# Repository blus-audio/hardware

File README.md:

# Blus hardware

This repository contains hardware designs for the blus series of audio equipment.

- The [blus mini](./blus-mini) - a small 4x25 W digital amplifier with DSP and various digital inputs.

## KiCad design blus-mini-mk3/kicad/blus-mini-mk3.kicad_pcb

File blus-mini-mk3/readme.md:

# Blus mini mk2

This small amplifier is ideally suited for stereo pairs of two-way speakers.

Find the [hardware design files](./kicad/) for reference.
It is required to flash the corresponding [firmware](https://github.com/blus-audio/firmware-rs).

## Features

- Source switching, digital signal processing, and more on a powerful STM32H723
- 4x25 W Class-D amplifiers - the [TI TAS2780](https://www.ti.com/product/TAS2780)
- USB Audio interface (UAC 1.0) with up to 48 kHz/32 bit audio
- Raspberry Pi header for direct I2S audio streaming
- S/PDIF input and output
- Auxiliary I2S input or output
- Full 32 bit digital audio chain with analog conversion only in the amplifiers

## State of development

The amplifier has been fully tested for an extended period of time.

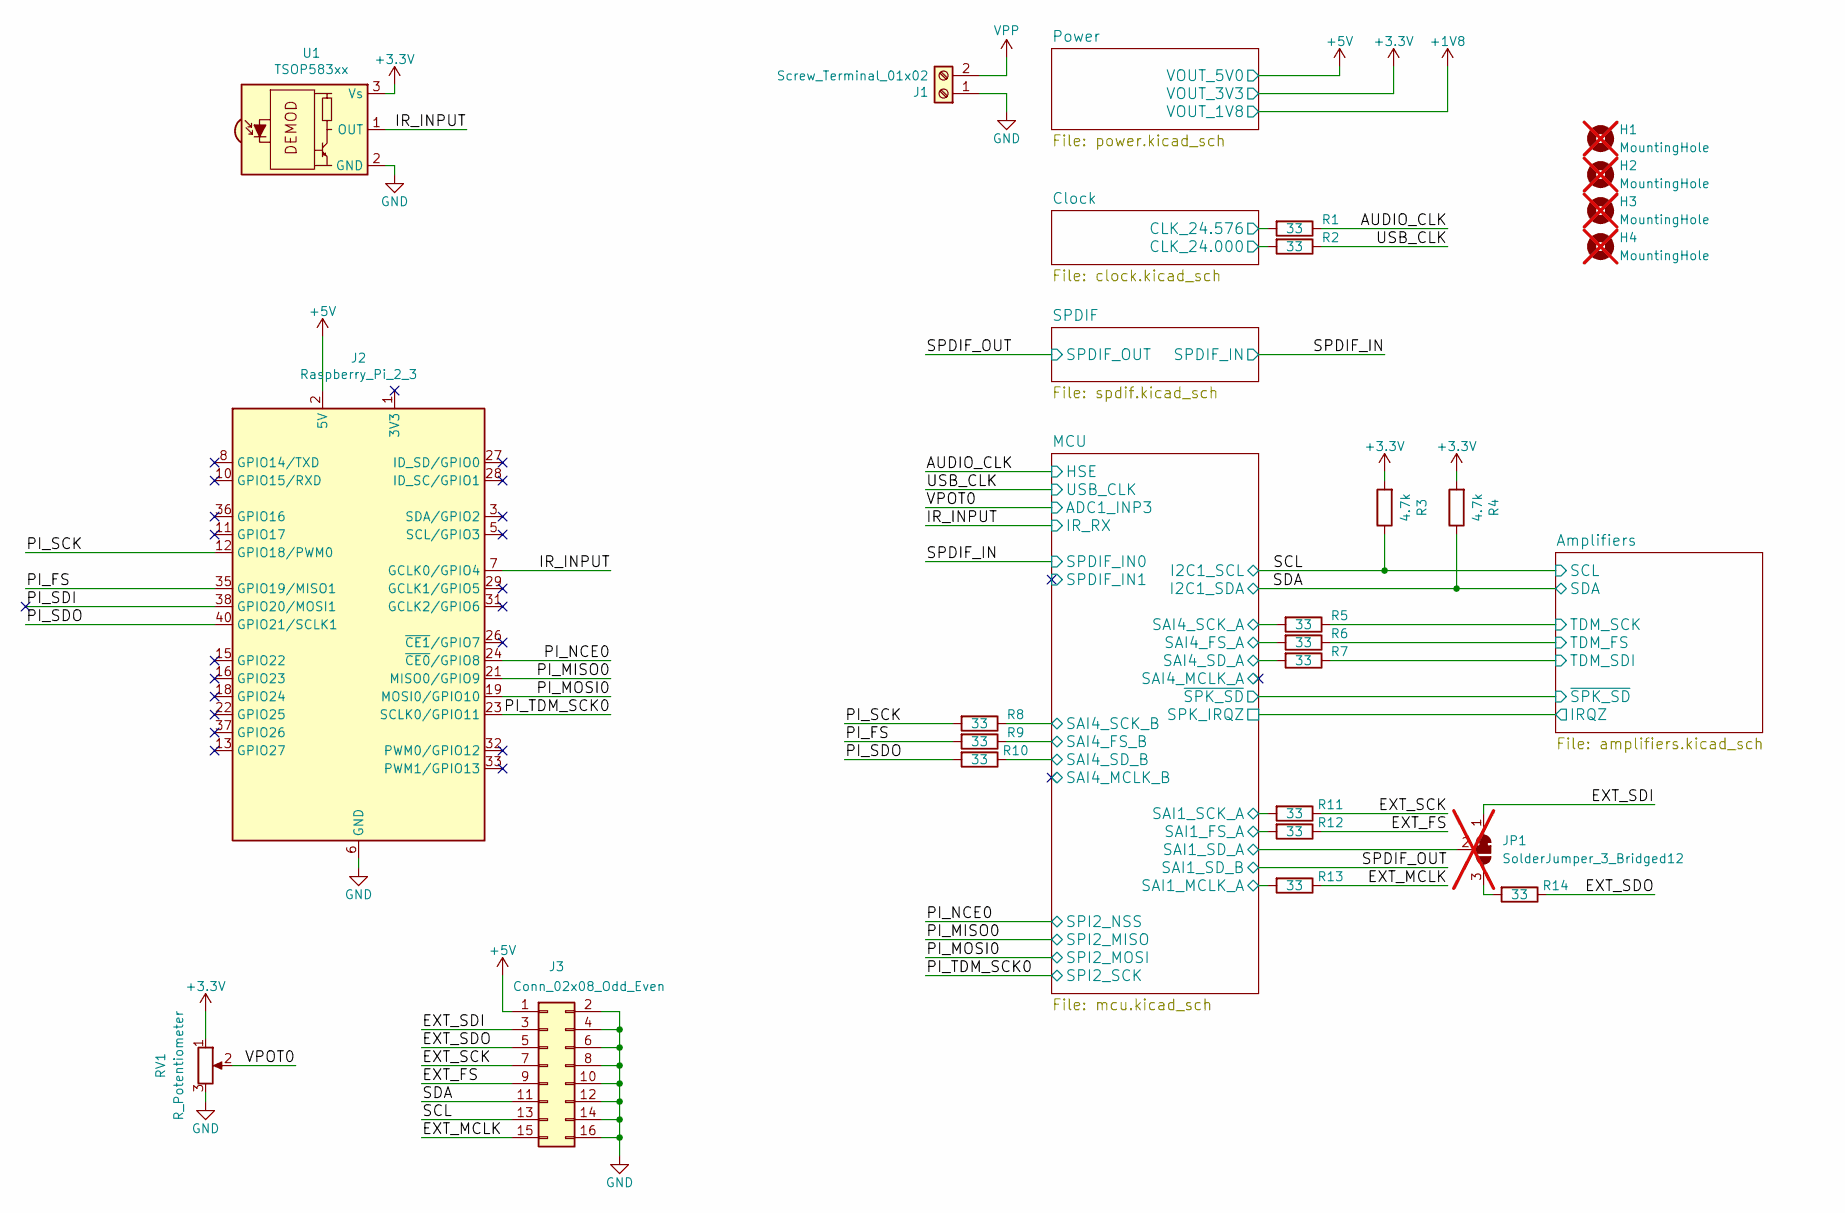
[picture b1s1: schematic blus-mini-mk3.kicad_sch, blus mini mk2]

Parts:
H1, H2, H3, H4: MountingHole; MountingHole_3.2mm_M3_ISO7380_Pad; not fitted
J1: Screw_Terminal_01x02; wuerth_691216410002
J2: Raspberry_Pi_2_3; PinSocket_2x20_P2.54mm_Vertical
J3: Conn_02x08_Odd_Even; IDC-Header_2x08_P2.54mm_Horizontal
JP1: SolderJumper_3_Bridged12; SolderJumper-3_P1.3mm_Bridged12_RoundedPad1.0x1.5mm; not fitted
R1, R2, R5, R6, R7, R8, R9, R10, R11, R12, R13, R14: 33; R_0402_1005Metric; MPN C25105
R3, R4: 4.7k; R_0402_1005Metric; MPN C25900
RV1: R_Potentiometer; Potentiometer_Bourns_PTV09A-1_Single_Vertical
U1: TSOP583xx; Vishay_MINICAST-3Pin

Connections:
+3.3V: R3.2, R4.2, RV1.1, U1.3 (Vs); also elsewhere on the board
+5V: J2.2 (5V), J2.4 (5V), J3.1; also elsewhere on the board
/AUDIO_CLK: R1.1; also elsewhere on the board
/Amplifiers/TDM_FS: R6.1; also elsewhere on the board
/Amplifiers/TDM_SCK: R5.1; also elsewhere on the board
/Amplifiers/TDM_SDI: R7.1; also elsewhere on the board
/Clock/CLK_24.000: R2.2; also elsewhere on the board
/Clock/CLK_24.576: R1.2; also elsewhere on the board
/EXT_FS: J3.9, R12.1
/EXT_MCLK: J3.15, R13.1
/EXT_SCK: J3.7, R11.1
/EXT_SDI: J3.3, JP1.1 (A)
/EXT_SDO: J3.5, R14.1
/IR_INPUT: J2.7 (GCLK0/GPIO4), U1.1 (OUT); also elsewhere on the board
/MCU/SAI1_FS_A: R12.2; also elsewhere on the board
/MCU/SAI1_MCLK_A: R13.2; also elsewhere on the board
/MCU/SAI1_SCK_A: R11.2; also elsewhere on the board
/MCU/SAI1_SD_A: JP1.2 (C); also elsewhere on the board
/MCU/SAI4_FS_A: R6.2; also elsewhere on the board
/MCU/SAI4_FS_B: R9.1; also elsewhere on the board
/MCU/SAI4_SCK_A: R5.2; also elsewhere on the board
/MCU/SAI4_SCK_B: R8.1; also elsewhere on the board
/MCU/SAI4_SD_A: R7.2; also elsewhere on the board
/MCU/SAI4_SD_B: R10.1; also elsewhere on the board
/PI_FS: J2.35 (GPIO19/MISO1), R9.2
/PI_MISO0: J2.21 (MISO0/GPIO9); also elsewhere on the board
/PI_MOSI0: J2.19 (MOSI0/GPIO10); also elsewhere on the board
/PI_NCE0: J2.24 (~CE0/GPIO8); also elsewhere on the board
/PI_SCK: J2.12 (GPIO18/PWM0), R8.2
/PI_SDI: J2.38 (GPIO20/MOSI1)
/PI_SDO: J2.40 (GPIO21/SCLK1), R10.2
/PI_TDM_SCK0: J2.23 (SCLK0/GPIO11); also elsewhere on the board
/SCL: J3.13, R3.1; also elsewhere on the board
/SDA: J3.11, R4.1; also elsewhere on the board
/USB_CLK: R2.1; also elsewhere on the board
/VPOT0: RV1.2; also elsewhere on the board
GND: J1.1, J2.6 (GND), J2.9 (GND), J2.14 (GND), J2.20 (GND), J2.25 (GND), J2.30 (GND), J2.34 (GND), J2.39 (GND), J3.2, J3.4, J3.6, J3.8, J3.10, J3.12, J3.14, J3.16, RV1.3, U1.2 (GND); also elsewhere on the board
unnamed: JP1.3 (B), R14.2
VPP: J1.2; also elsewhere on the board

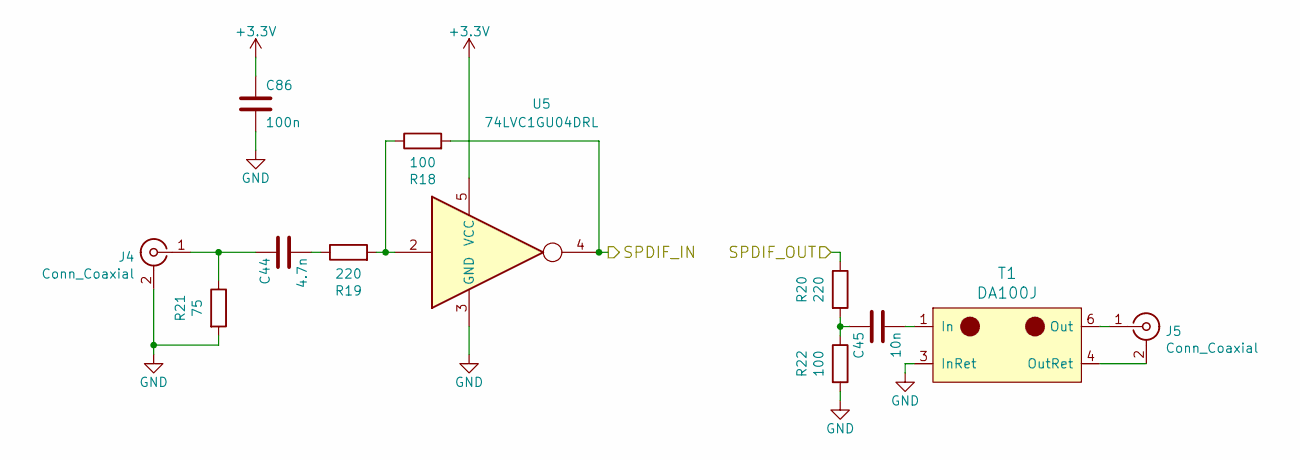
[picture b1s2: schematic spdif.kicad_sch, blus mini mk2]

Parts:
C44: 4.7n; C_0402_1005Metric
C45: 10n; C_0402_1005Metric; MPN C15195
C86: 100n; C_0402_1005Metric; MPN C307331
J4, J5: Conn_Coaxial; cui_rcj_02x
R18, R22: 100; R_0402_1005Metric; MPN C25076
R19, R20: 220; R_0402_1005Metric; MPN C25091
R21: 75; R_0402_1005Metric; MPN C25133
T1: DA100J; SOIC-6
U5: 74LVC1GU04DRL; SOT-553; MPN C2877548

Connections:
+3.3V: C86.1, U5.5 (VCC); also elsewhere on the board
/SPDIF_IN: R18.2, U5.4; also elsewhere on the board
/SPDIF_OUT: R20.1; also elsewhere on the board
GND: C86.2, J4.2 (Ext), R21.2, R22.2, T1.3 (InRet), U5.3 (GND); also elsewhere on the board
unnamed: C44.2, R19.1
unnamed: C45.1, R20.2, R22.1
unnamed: C44.1, J4.1 (In), R21.1
unnamed: J5.2 (Ext), T1.4 (OutRet)
unnamed: J5.1 (In), T1.6 (Out)
unnamed: R18.1, R19.2, U5.2
unnamed: C45.2, T1.1 (In)

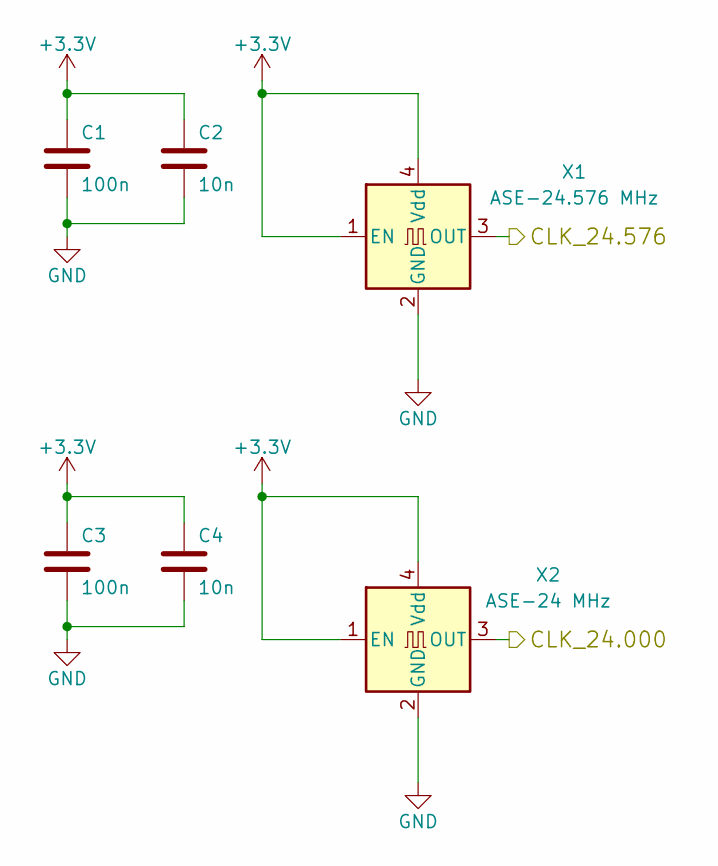
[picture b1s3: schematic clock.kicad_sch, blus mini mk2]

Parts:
C1, C3: 100n; C_0402_1005Metric; MPN C307331
C2, C4: 10n; C_0402_1005Metric; MPN C15195
X1: ASE-24.576 MHz; Oscillator_SMD_Abracon_ASE-4Pin_3.2x2.5mm
X2: ASE-24 MHz; Oscillator_SMD_Abracon_ASE-4Pin_3.2x2.5mm; MPN C507379

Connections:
+3.3V: C1.1, C2.1, C3.1, C4.1, X1.1 (EN), X1.4 (Vdd), X2.1 (EN), X2.4 (Vdd); also elsewhere on the board
/Clock/CLK_24.000: X2.3 (OUT); also elsewhere on the board
/Clock/CLK_24.576: X1.3 (OUT); also elsewhere on the board
GND: C1.2, C2.2, C3.2, C4.2, X1.2 (GND), X2.2 (GND); also elsewhere on the board

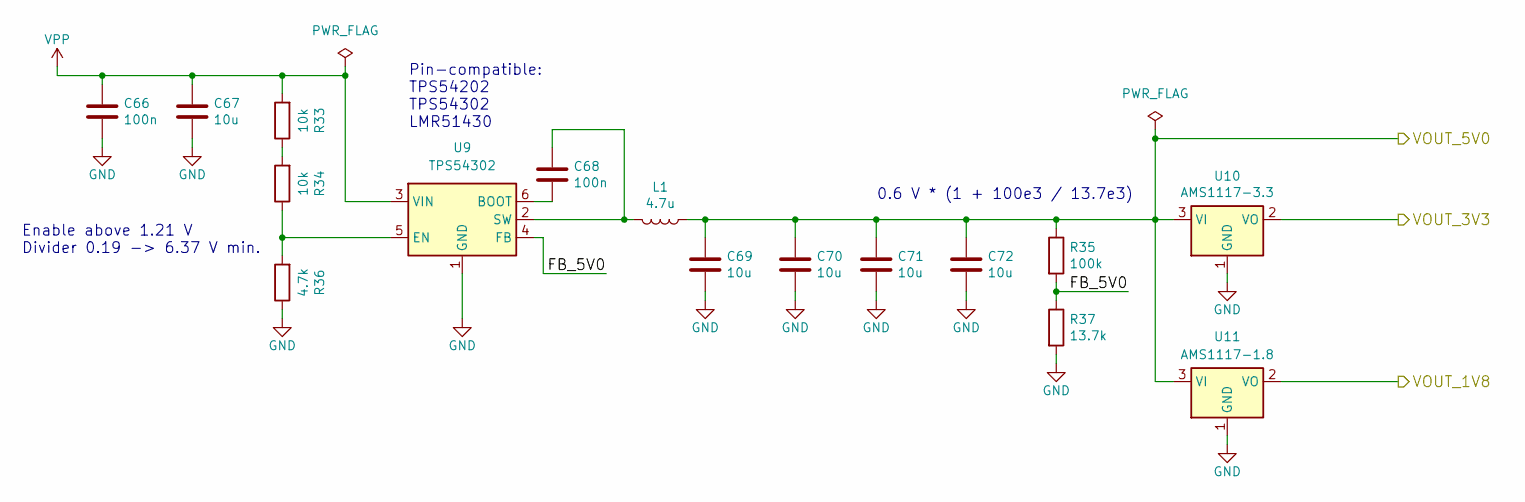
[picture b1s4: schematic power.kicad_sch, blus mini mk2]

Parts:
C66, C68: 100n; C_0402_1005Metric; MPN C307331
C67, C69, C70, C71, C72: 10u; C_1206_3216Metric; MPN C13585
L1: 4.7u; L_Abracon_ASPI-0630LR; MPN C167220
R33, R34: 10k; R_0402_1005Metric; MPN C25744
R35: 100k; R_0402_1005Metric; MPN C25741
R36: 4.7k; R_0402_1005Metric; MPN C25900
R37: 13.7k; R_0402_1005Metric
U9: TPS54302; SOT-23-6; MPN C311983; JLCPCB Rotation Offset -90
U10: AMS1117-3.3; SOT-223-3_TabPin2; MPN C6186
U11: AMS1117-1.8; SOT-223-3_TabPin2; MPN C6185

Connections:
+1V8: U11.2 (VO); also elsewhere on the board
+3.3V: U10.2 (VO); also elsewhere on the board
+5V: C69.1, C70.1, C71.1, C72.1, L1.1, R35.1, U10.3 (VI), U11.3 (VI); also elsewhere on the board
/Power/FB_5V0: R35.2, R37.1, U9.4 (FB)
GND: C66.2, C67.2, C69.2, C70.2, C71.2, C72.2, R36.1, R37.2, U9.1 (GND), U10.1 (GND), U11.1 (GND); also elsewhere on the board
unnamed: R33.1, R34.2
unnamed: C68.2, U9.6 (BOOT)
unnamed: R34.1, R36.2, U9.5 (EN)
unnamed: C68.1, L1.2, U9.2 (SW)
VPP: C66.1, C67.1, R33.2, U9.3 (VIN); also elsewhere on the board

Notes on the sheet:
0.6 V * (1 + 100e3 / 13.7e3)
Pin-compatible: TPS54202 TPS54302 LMR51430
Enable above 1.21 V Divider 0.19 -> 6.37 V min.

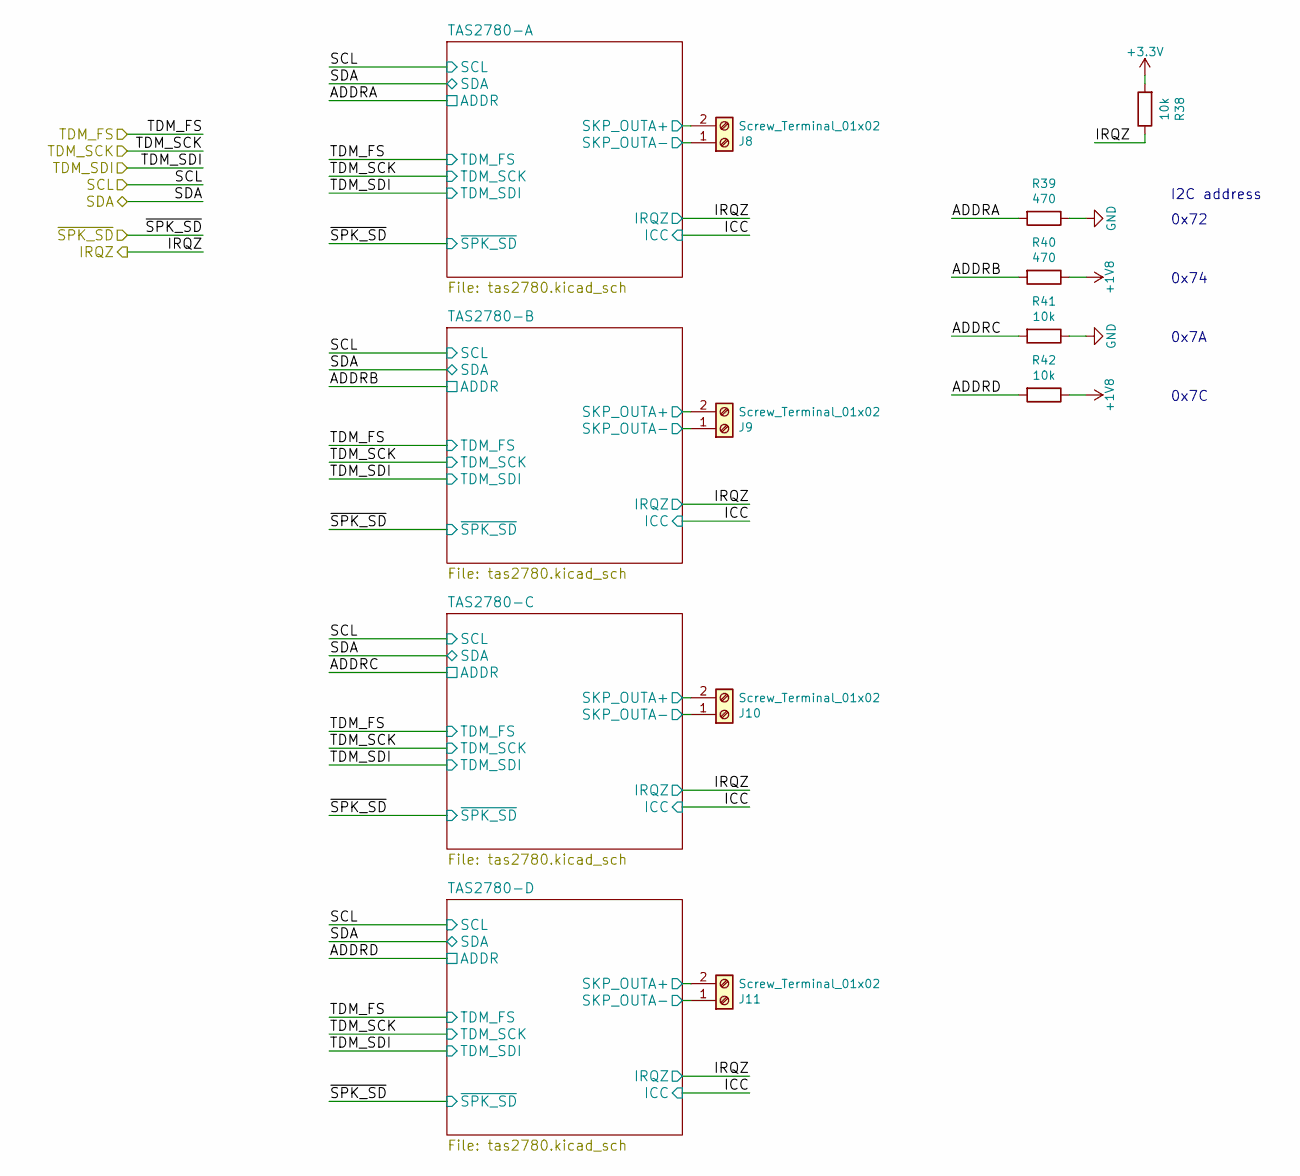
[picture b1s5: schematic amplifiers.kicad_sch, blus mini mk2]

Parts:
J8, J9, J10, J11: Screw_Terminal_01x02; wuerth_691216410002
R38, R41, R42: 10k; R_0402_1005Metric; MPN C25744
R39, R40: 470; R_0402_1005Metric; MPN C25117

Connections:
+1V8: R40.1, R42.1; also elsewhere on the board
+3.3V: R38.2; also elsewhere on the board
/Amplifiers/ADDRA: R39.2; also elsewhere on the board
/Amplifiers/ADDRB: R40.2; also elsewhere on the board
/Amplifiers/ADDRC: R41.2; also elsewhere on the board
/Amplifiers/ADDRD: R42.2; also elsewhere on the board
/Amplifiers/IRQZ: R38.1; also elsewhere on the board
/Amplifiers/TAS2780-A/SKP_OUTA+: J8.2; also elsewhere on the board
/Amplifiers/TAS2780-A/SKP_OUTA-: J8.1; also elsewhere on the board
/Amplifiers/TAS2780-B/SKP_OUTA+: J9.2; also elsewhere on the board
/Amplifiers/TAS2780-B/SKP_OUTA-: J9.1; also elsewhere on the board
/Amplifiers/TAS2780-C/SKP_OUTA+: J10.2; also elsewhere on the board
/Amplifiers/TAS2780-C/SKP_OUTA-: J10.1; also elsewhere on the board
/Amplifiers/TAS2780-D/SKP_OUTA+: J11.2; also elsewhere on the board
/Amplifiers/TAS2780-D/SKP_OUTA-: J11.1; also elsewhere on the board
GND: R39.1, R41.1; also elsewhere on the board

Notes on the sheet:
0x7C
0x72
0x7A
I2C address
0x74

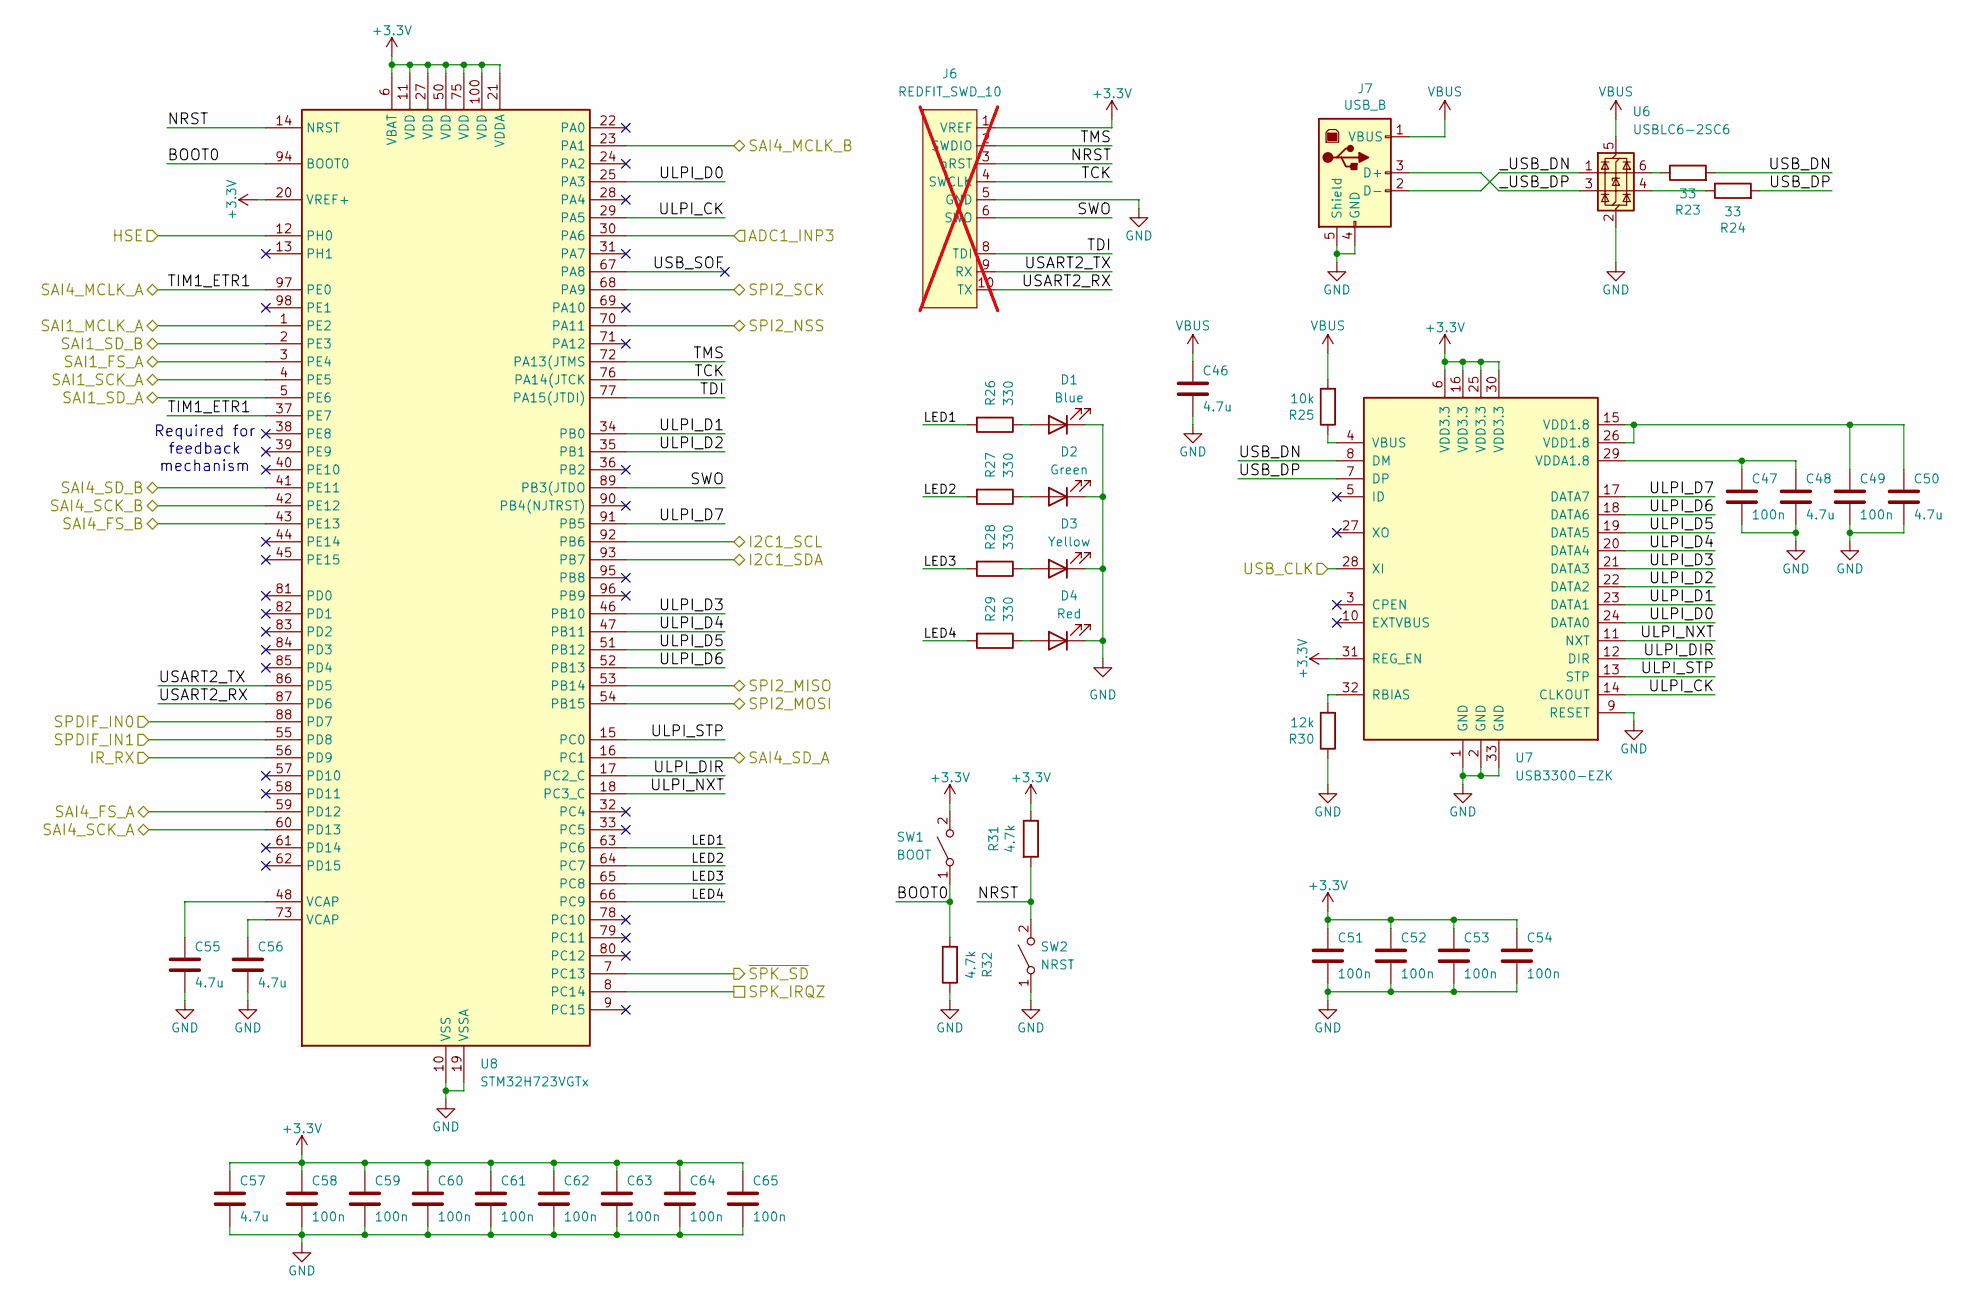
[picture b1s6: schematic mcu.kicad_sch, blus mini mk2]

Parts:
C46, C48, C50, C55, C56, C57: 4.7u; C_0805_2012Metric; MPN C1779
C47, C49, C51, C52, C53, C54, C58, C59, C60, C61, C62, C63, C64, C65: 100n; C_0402_1005Metric; MPN C307331
D1: Blue; LED_0603_1608Metric; MPN C72041
D2: Green; LED_0603_1608Metric; MPN C72043
D3: Yellow; LED_0603_1608Metric; MPN C72038
D4: Red; LED_0603_1608Metric; MPN C2286
J6: REDFIT_SWD_10; WR-WST REDFIT IDC 6 10 DBG; not fitted
J7: USB_B; USB_B_TE_5787834_Vertical; MPN C592900
R23, R24: 33; R_0402_1005Metric; MPN C25105
R25: 10k; R_0402_1005Metric; MPN C25744
R26, R27, R28, R29: 330; R_0402_1005Metric; MPN C25104
R30: 12k; R_0402_1005Metric; MPN C25752
R31, R32: 4.7k; R_0402_1005Metric; MPN C25900
SW1: BOOT; SW_SPST_TL3342; MPN C318884
SW2: NRST; SW_SPST_TL3342; MPN C318884
U6: USBLC6-2SC6; SOT-23-6; MPN C7519; JLCPCB Rotation Offset 90
U7: USB3300-EZK; QFN-32-1EP_5x5mm_P0.5mm_EP3.45x3.45mm; MPN C108383; JLCPCB Rotation Offset 180
U8: STM32H723VGTx; LQFP-100_14x14mm_P0.5mm; MPN C730142

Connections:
+3.3V: C51.1, C52.1, C53.1, C54.1, C57.1, C58.1, C59.1, C60.1, C61.1, C62.1, C63.1, C64.1, C65.1, J6.1 (VREF), R31.1, SW1.2 (B), U7.6 (VDD3.3), U7.16 (VDD3.3), U7.25 (VDD3.3), U7.30 (VDD3.3), U7.31 (REG_EN), U8.6 (VBAT), U8.11 (VDD), U8.20 (VREF+), U8.21 (VDDA), U8.27 (VDD), U8.50 (VDD), U8.75 (VDD), U8.100 (VDD); also elsewhere on the board
/AUDIO_CLK: U8.12 (PH0); also elsewhere on the board
/Amplifiers/IRQZ: U8.8 (PC14); also elsewhere on the board
/Amplifiers/~SPK_SD: U8.7 (PC13); also elsewhere on the board
/IR_INPUT: U8.56 (PD9); also elsewhere on the board
/MCU/BOOT0: R32.2, SW1.1 (A), U8.94 (BOOT0)
/MCU/LED1: R26.2, U8.63 (PC6)
/MCU/LED2: R27.2, U8.64 (PC7)
/MCU/LED3: R28.2, U8.65 (PC8)
/MCU/LED4: R29.2, U8.66 (PC9)
/MCU/NRST: J6.3 (nRST), R31.2, SW2.2 (B), U8.14 (NRST)
/MCU/SAI1_FS_A: U8.3 (PE4); also elsewhere on the board
/MCU/SAI1_MCLK_A: U8.1 (PE2); also elsewhere on the board
/MCU/SAI1_SCK_A: U8.4 (PE5); also elsewhere on the board
/MCU/SAI1_SD_A: U8.5 (PE6); also elsewhere on the board
/MCU/SAI4_FS_A: U8.59 (PD12); also elsewhere on the board
/MCU/SAI4_FS_B: U8.43 (PE13); also elsewhere on the board
/MCU/SAI4_MCLK_B: U8.23 (PA1)
/MCU/SAI4_SCK_A: U8.60 (PD13); also elsewhere on the board
/MCU/SAI4_SCK_B: U8.42 (PE12); also elsewhere on the board
/MCU/SAI4_SD_A: U8.16 (PC1); also elsewhere on the board
/MCU/SAI4_SD_B: U8.41 (PE11); also elsewhere on the board
/MCU/SPDIF_IN1: U8.55 (PD8)
/MCU/SWO: J6.6 (SWO), U8.89 (PB3(JTDO)
/MCU/TCK: J6.4 (SWCLK), U8.76 (PA14(JTCK)
/MCU/TDI: J6.8 (TDI), U8.77 (PA15(JTDI))
/MCU/TIM1_ETR1: U8.37 (PE7), U8.97 (PE0)
/MCU/TMS: J6.2 (SWDIO), U8.72 (PA13(JTMS)
/MCU/ULPI_CK: U7.14 (CLKOUT), U8.29 (PA5)
/MCU/ULPI_D0: U7.24 (DATA0), U8.25 (PA3)
/MCU/ULPI_D1: U7.23 (DATA1), U8.34 (PB0)
/MCU/ULPI_D2: U7.22 (DATA2), U8.35 (PB1)
/MCU/ULPI_D3: U7.21 (DATA3), U8.46 (PB10)
/MCU/ULPI_D4: U7.20 (DATA4), U8.47 (PB11)
/MCU/ULPI_D5: U7.19 (DATA5), U8.51 (PB12)
/MCU/ULPI_D6: U7.18 (DATA6), U8.52 (PB13)
/MCU/ULPI_D7: U7.17 (DATA7), U8.91 (PB5)
/MCU/ULPI_DIR: U7.12 (DIR), U8.17 (PC2_C)
/MCU/ULPI_NXT: U7.11 (NXT), U8.18 (PC3_C)
/MCU/ULPI_STP: U7.13 (STP), U8.15 (PC0)
/MCU/USART2_RX: J6.10 (TX), U8.87 (PD6)
/MCU/USART2_TX: J6.9 (RX), U8.86 (PD5)
/MCU/USB_DN: R23.2, U7.8 (DM)
/MCU/USB_DP: R24.2, U7.7 (DP)
/MCU/USB_SOF: U8.67 (PA8)
/MCU/_USB_DN: J7.2 (D-), U6.1 (I/O1)
/MCU/_USB_DP: J7.3 (D+), U6.3 (I/O2)
/PI_MISO0: U8.53 (PB14); also elsewhere on the board
/PI_MOSI0: U8.54 (PB15); also elsewhere on the board
/PI_NCE0: U8.70 (PA11); also elsewhere on the board
/PI_TDM_SCK0: U8.68 (PA9); also elsewhere on the board
/SCL: U8.92 (PB6); also elsewhere on the board
/SDA: U8.93 (PB7); also elsewhere on the board
/SPDIF_IN: U8.88 (PD7); also elsewhere on the board
/SPDIF_OUT: U8.2 (PE3); also elsewhere on the board
/USB_CLK: U7.28 (XI); also elsewhere on the board
/VPOT0: U8.30 (PA6); also elsewhere on the board
GND: C46.2, C47.2, C48.2, C49.2, C50.2, C51.2, C52.2, C53.2, C54.2, C55.2, C56.2, C57.2, C58.2, C59.2, C60.2, C61.2, C62.2, C63.2, C64.2, C65.2, D1.1 (K), D2.1 (K), D3.1 (K), D4.1 (K), J6.5 (GND), J7.4 (GND), J7.5 (Shield), R30.1, R32.1, SW2.1 (A), U6.2 (GND), U7.1 (GND), U7.2 (GND), U7.9 (RESET), U7.33 (GND), U8.10 (VSS), U8.19 (VSSA), U8.26 (VSS), U8.49 (VSS), U8.74 (VSS), U8.99 (VSS); also elsewhere on the board
unnamed: C49.1, C50.1, U7.15 (VDD1.8), U7.26 (VDD1.8)
unnamed: C55.1, U8.48 (VCAP)
unnamed: C56.1, U8.73 (VCAP)
unnamed: D1.2 (A), R26.1
unnamed: D2.2 (A), R27.1
unnamed: D3.2 (A), R28.1
unnamed: D4.2 (A), R29.1
unnamed: R23.1, U6.6 (I/O1)
unnamed: R24.1, U6.4 (I/O2)
unnamed: R30.2, U7.32 (RBIAS)
unnamed: R25.1, U7.4 (VBUS)
unnamed: C47.1, C48.1, U7.29 (VDDA1.8)
VBUS: C46.1, J7.1 (VBUS), R25.2, U6.5 (VBUS)

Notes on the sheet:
Required for feedback mechanism

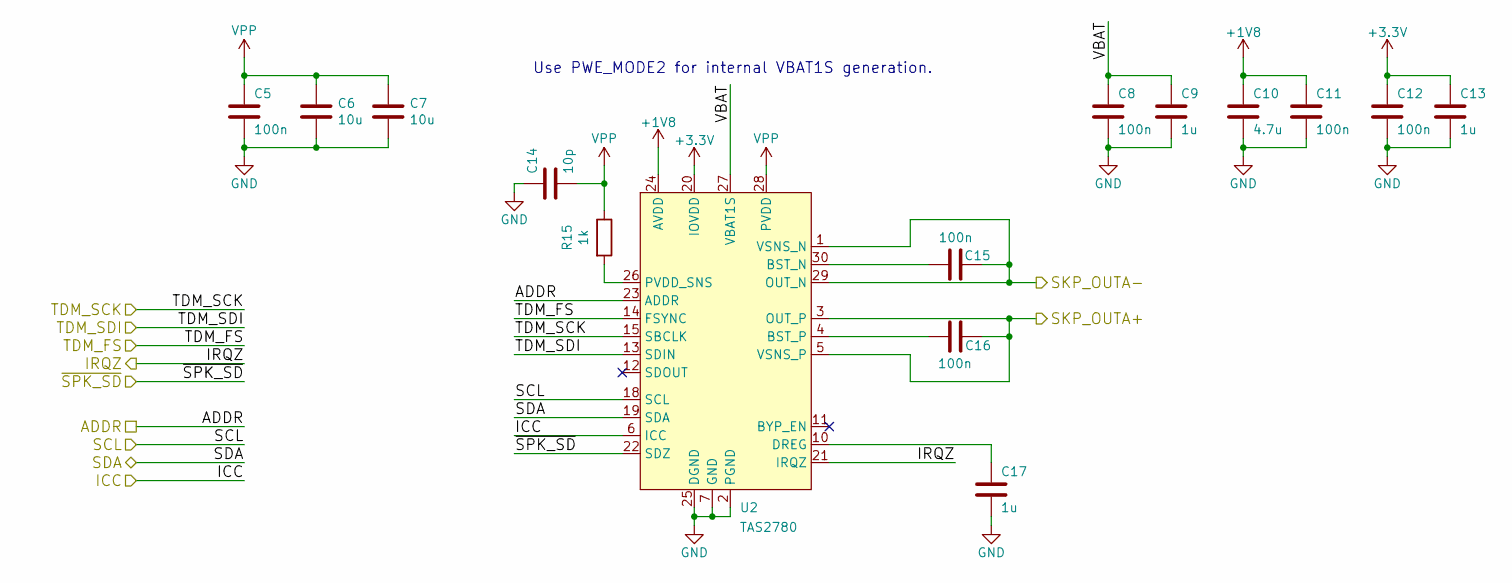
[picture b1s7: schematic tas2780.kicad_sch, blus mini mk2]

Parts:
C5, C8, C11, C12, C15, C16: 100n; C_0402_1005Metric; MPN C307331
C6, C7: 10u; C_1206_3216Metric; MPN C13585
C9, C13, C17: 1u; C_0603_1608Metric; MPN C15849
C10: 4.7u; C_0805_2012Metric; MPN C1779
C14: 10p; C_0402_1005Metric; MPN C32949
R15: 1k; R_0402_1005Metric; MPN C11702
U2: TAS2780; TI-30-Pin-HR-QFN; MPN C5214951

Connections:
+1V8: C10.1, C11.1, U2.24 (AVDD); also elsewhere on the board
+3.3V: C12.1, C13.1, U2.20 (IOVDD); also elsewhere on the board
/Amplifiers/ADDRA: U2.23 (ADDR); also elsewhere on the board
/Amplifiers/ICC: U2.6 (ICC); also elsewhere on the board
/Amplifiers/IRQZ: U2.21 (IRQZ); also elsewhere on the board
/Amplifiers/TAS2780-A/SKP_OUTA+: C16.1, U2.3 (OUT_P), U2.5 (VSNS_P); also elsewhere on the board
/Amplifiers/TAS2780-A/SKP_OUTA-: C15.2, U2.1 (VSNS_N), U2.29 (OUT_N); also elsewhere on the board
/Amplifiers/TAS2780-A/VBAT: C8.1, C9.1, U2.27 (VBAT1S)
/Amplifiers/TDM_FS: U2.14 (FSYNC); also elsewhere on the board
/Amplifiers/TDM_SCK: U2.15 (SBCLK); also elsewhere on the board
/Amplifiers/TDM_SDI: U2.13 (SDIN); also elsewhere on the board
/Amplifiers/~SPK_SD: U2.22 (SDZ); also elsewhere on the board
/SCL: U2.18 (SCL); also elsewhere on the board
/SDA: U2.19 (SDA); also elsewhere on the board
GND: C5.2, C6.2, C7.2, C8.2, C9.2, C10.2, C11.2, C12.2, C13.2, C14.1, C17.2, U2.2 (PGND), U2.7 (GND), U2.25 (DGND); also elsewhere on the board
unnamed: C15.1, U2.30 (BST_N)
unnamed: C16.2, U2.4 (BST_P)
unnamed: C17.1, U2.10 (DREG)
unnamed: R15.2, U2.26 (PVDD_SNS)
VPP: C5.1, C6.1, C7.1, C14.2, R15.1, U2.28 (PVDD); also elsewhere on the board

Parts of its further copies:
C18, C21, C24, C25, C28, C29, C31, C34, C37, C38, C41, C42, C73, C76, C79, C80, C83, C84: 100n; C_0402_1005Metric; MPN C307331
C19, C20, C32, C33, C74, C75: 10u; C_1206_3216Metric; MPN C13585
C22, C26, C30, C35, C39, C43, C77, C81, C85: 1u; C_0603_1608Metric; MPN C15849
C23, C36, C78: 4.7u; C_0805_2012Metric; MPN C1779
C27, C40, C82: 10p; C_0402_1005Metric; MPN C32949
R16, R17, R43: 1k; R_0402_1005Metric; MPN C11702
U3, U4, U12: TAS2780; TI-30-Pin-HR-QFN; MPN C5214951

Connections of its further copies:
+1V8: C23.1, C24.1, C36.1, C37.1, C78.1, C79.1, U3.24 (AVDD), U4.24 (AVDD), U12.24 (AVDD); also elsewhere on the board
+3.3V: C25.1, C26.1, C38.1, C39.1, C80.1, C81.1, U3.20 (IOVDD), U4.20 (IOVDD), U12.20 (IOVDD); also elsewhere on the board
/Amplifiers/ADDRB: U12.23 (ADDR); also elsewhere on the board
/Amplifiers/ADDRC: U3.23 (ADDR); also elsewhere on the board
/Amplifiers/ADDRD: U4.23 (ADDR); also elsewhere on the board
/Amplifiers/ICC: U3.6 (ICC), U4.6 (ICC), U12.6 (ICC); also elsewhere on the board
/Amplifiers/IRQZ: U3.21 (IRQZ), U4.21 (IRQZ), U12.21 (IRQZ); also elsewhere on the board
/Amplifiers/TAS2780-B/SKP_OUTA+: C84.1, U12.3 (OUT_P), U12.5 (VSNS_P); also elsewhere on the board
/Amplifiers/TAS2780-B/SKP_OUTA-: C83.2, U12.1 (VSNS_N), U12.29 (OUT_N); also elsewhere on the board
/Amplifiers/TAS2780-B/VBAT: C76.1, C77.1, U12.27 (VBAT1S)
/Amplifiers/TAS2780-C/SKP_OUTA+: C29.1, U3.3 (OUT_P), U3.5 (VSNS_P); also elsewhere on the board
/Amplifiers/TAS2780-C/SKP_OUTA-: C28.2, U3.1 (VSNS_N), U3.29 (OUT_N); also elsewhere on the board
/Amplifiers/TAS2780-C/VBAT: C21.1, C22.1, U3.27 (VBAT1S)
/Amplifiers/TAS2780-D/SKP_OUTA+: C42.1, U4.3 (OUT_P), U4.5 (VSNS_P); also elsewhere on the board
/Amplifiers/TAS2780-D/SKP_OUTA-: C41.2, U4.1 (VSNS_N), U4.29 (OUT_N); also elsewhere on the board
/Amplifiers/TAS2780-D/VBAT: C34.1, C35.1, U4.27 (VBAT1S)
/Amplifiers/TDM_FS: U3.14 (FSYNC), U4.14 (FSYNC), U12.14 (FSYNC); also elsewhere on the board
/Amplifiers/TDM_SCK: U3.15 (SBCLK), U4.15 (SBCLK), U12.15 (SBCLK); also elsewhere on the board
/Amplifiers/TDM_SDI: U3.13 (SDIN), U4.13 (SDIN), U12.13 (SDIN); also elsewhere on the board
/Amplifiers/~SPK_SD: U3.22 (SDZ), U4.22 (SDZ), U12.22 (SDZ); also elsewhere on the board
/SCL: U3.18 (SCL), U4.18 (SCL), U12.18 (SCL); also elsewhere on the board
/SDA: U3.19 (SDA), U4.19 (SDA), U12.19 (SDA); also elsewhere on the board
GND: C18.2, C19.2, C20.2, C21.2, C22.2, C23.2, C24.2, C25.2, C26.2, C27.1, C30.2, C31.2, C32.2, C33.2, C34.2, C35.2, C36.2, C37.2, C38.2, C39.2, C40.1, C43.2, C73.2, C74.2, C75.2, C76.2, C77.2, C78.2, C79.2, C80.2, C81.2, C82.1, C85.2, U3.2 (PGND), U3.7 (GND), U3.25 (DGND), U4.2 (PGND), U4.7 (GND), U4.25 (DGND), U12.2 (PGND), U12.7 (GND), U12.25 (DGND); also elsewhere on the board
unnamed: C28.1, U3.30 (BST_N)
unnamed: C29.2, U3.4 (BST_P)
unnamed: C30.1, U3.10 (DREG)
unnamed: R16.2, U3.26 (PVDD_SNS)
unnamed: C41.1, U4.30 (BST_N)
unnamed: C42.2, U4.4 (BST_P)
unnamed: C43.1, U4.10 (DREG)
unnamed: R17.2, U4.26 (PVDD_SNS)
unnamed: C83.1, U12.30 (BST_N)
unnamed: C84.2, U12.4 (BST_P)
unnamed: C85.1, U12.10 (DREG)
unnamed: R43.2, U12.26 (PVDD_SNS)
VPP: C18.1, C19.1, C20.1, C27.2, C31.1, C32.1, C33.1, C40.2, C73.1, C74.1, C75.1, C82.2, R16.1, R17.1, R43.1, U3.28 (PVDD), U4.28 (PVDD), U12.28 (PVDD); also elsewhere on the board

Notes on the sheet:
Use PWE_MODE2 for internal VBAT1S generation.

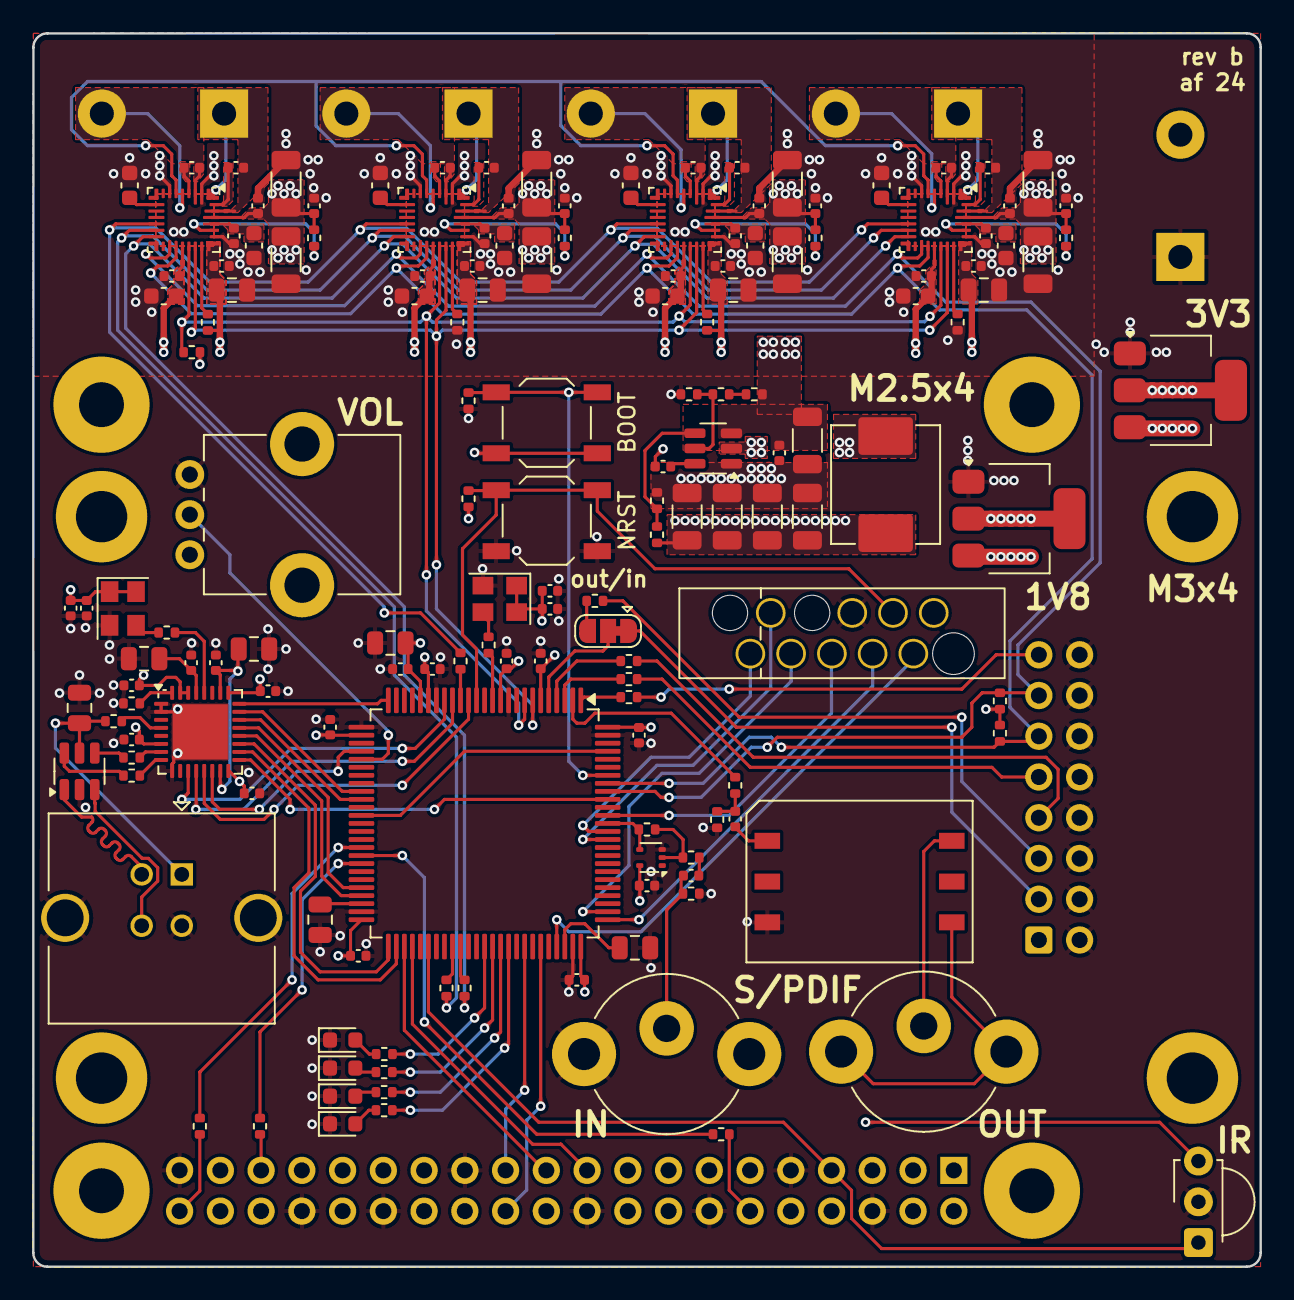
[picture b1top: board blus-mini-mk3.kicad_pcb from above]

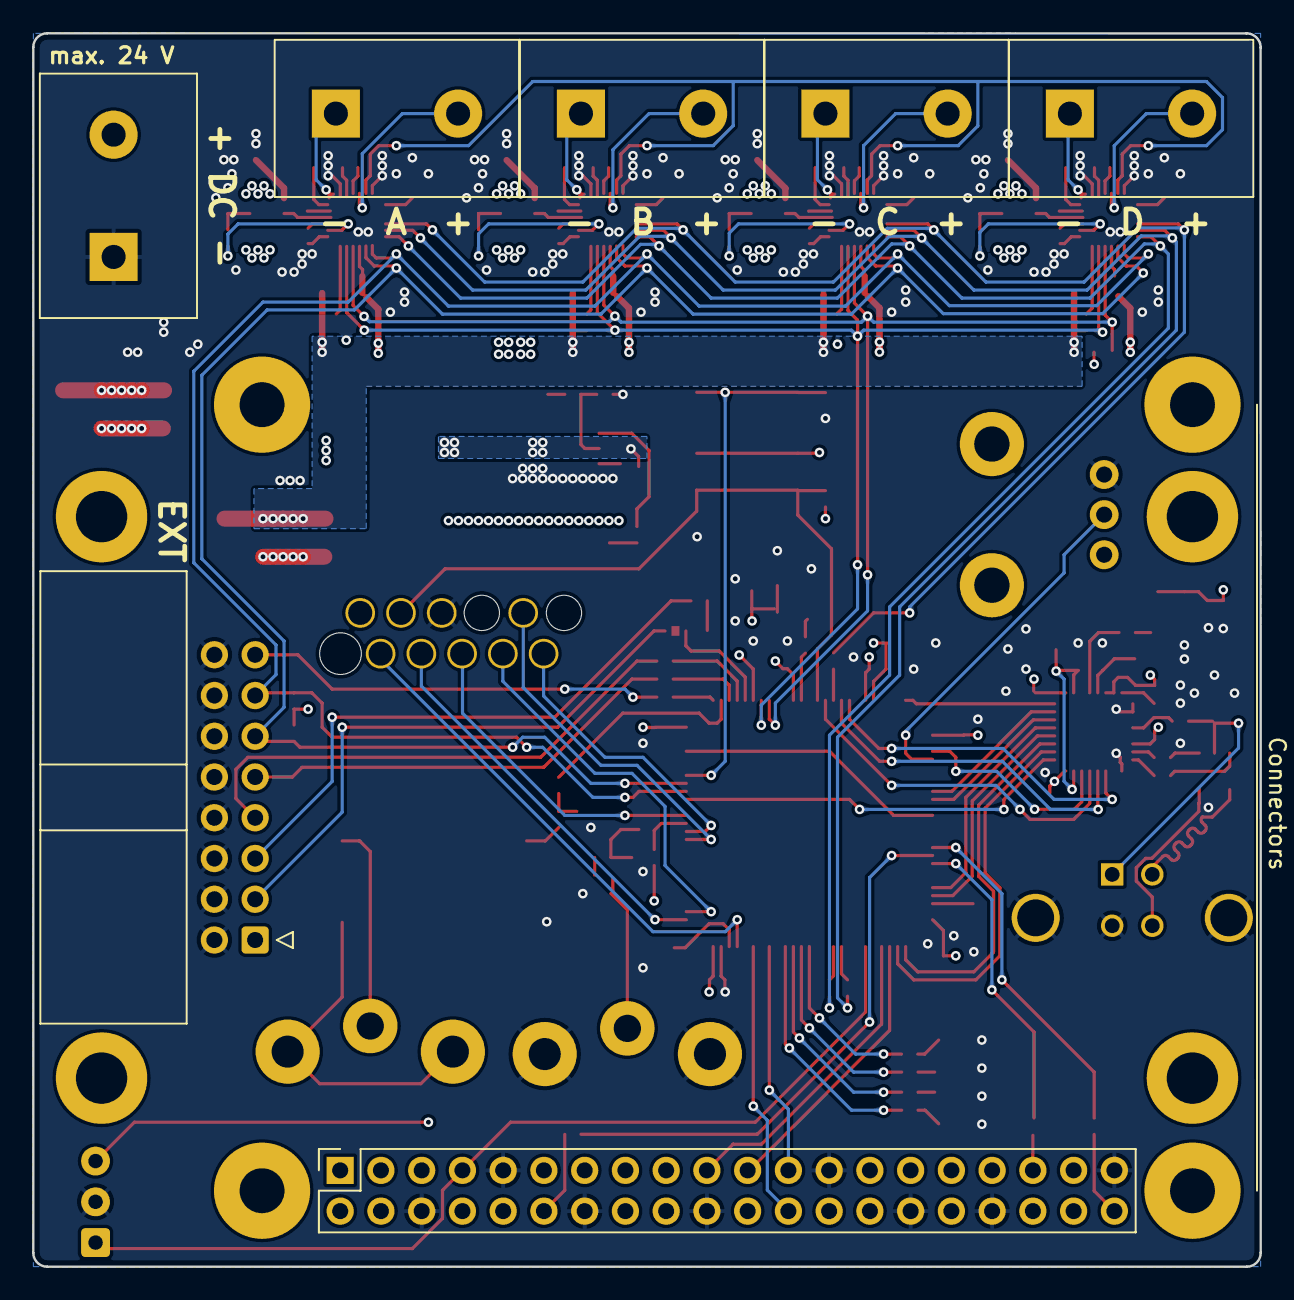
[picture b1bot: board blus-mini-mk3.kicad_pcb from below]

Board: 4 copper layers, 76.5 x 76.9 mm, 168 parts (7 on the bottom side), 130 nets.
